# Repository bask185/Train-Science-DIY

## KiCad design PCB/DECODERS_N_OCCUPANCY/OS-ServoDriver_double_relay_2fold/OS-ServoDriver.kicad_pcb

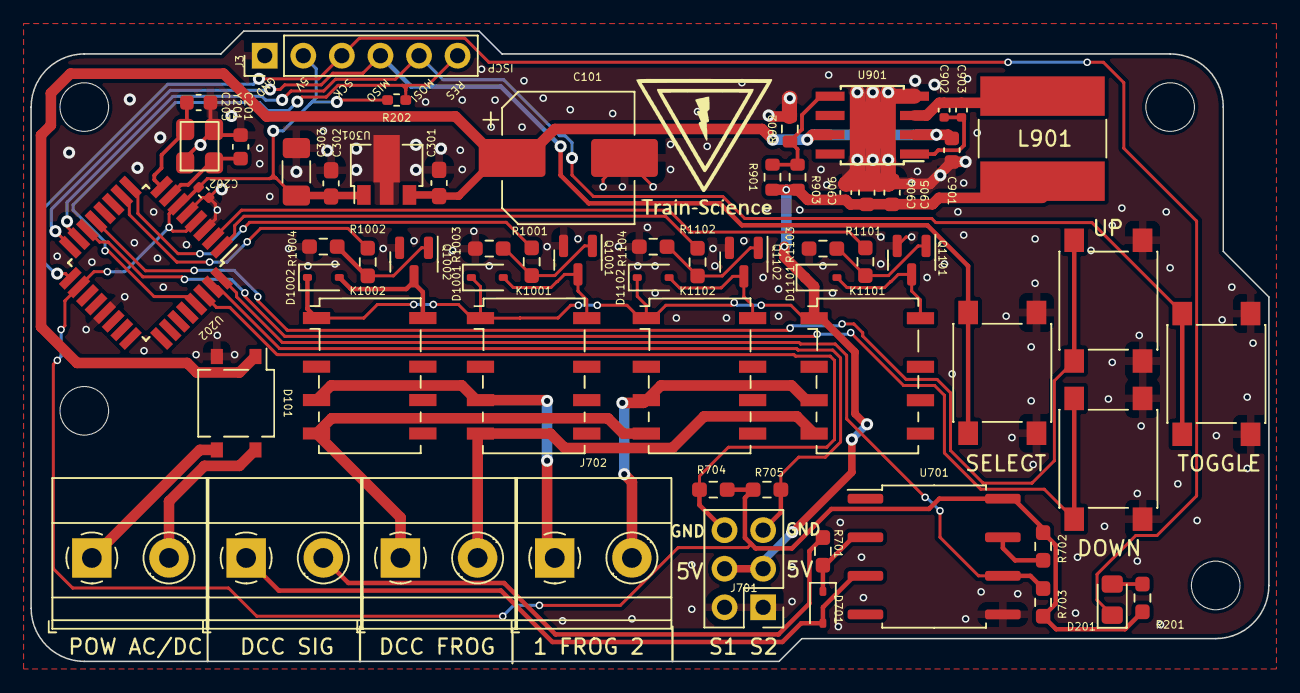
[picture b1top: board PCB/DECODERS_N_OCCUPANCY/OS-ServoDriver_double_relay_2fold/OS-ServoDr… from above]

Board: 2 copper layers, 81.5 x 41.5 mm, 62 parts (0 on the bottom side), 41 nets.

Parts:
C101: 1000uF; CP_Elec_8x10.5
C201, C203: 12pF; C_0603_1608Metric
C202, C902, C906: 100nF; C_0402_1005Metric
C301: 330nF; C_0603_1608Metric_Pad1.08x0.95mm_HandSolder
C302: 100nF; C_0603_1608Metric_Pad1.08x0.95mm_HandSolder
C303: 100uF; C_1206_3216Metric_Pad1.33x1.80mm_HandSolder
C901, C904, C905: 22uF; C_0603_1608Metric
C903: 22nF; C_0402_1005Metric
D101: MB10S; TO-269AA
D201: LED; LED_0805_2012Metric_Pad1.15x1.40mm_HandSolder
D701, D1001, D1002, D1101, D1102: 1N4148WS; D_SOD-323
J3: ICSP; PinHeader_1x06_P2.54mm_Vertical
J101: POWER; TerminalBlock_Phoenix_MKDS-1,5-2-5.08_1x02_P5.08mm_Horizont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
J102: DCC_FROG; TerminalBlock_Phoenix_MKDS-1,5-2-5.08_1x02_P5.08mm_Horizont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
J103: DCC_SIGNAL; TerminalBlock_Phoenix_MKDS-1,5-2-5.08_1x02_P5.08mm_Horizont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
J701: Servo; PinHeader_2x03_P2.54mm_Vertical
J702: Frogs; TerminalBlock_Phoenix_MKDS-1,5-2-5.08_1x02_P5.08mm_Horizont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
K1001, K1002, K1101, K1102: G6K-2F-Y-TR DC5; Relay_DPDT_Omron_G6K-2F-Y
L901: L; L_Bourns-SRN8040_8x8.15mm
Q1001, Q1002, Q1101, Q1102: AO3400A; SOT-23
R201: 6k2; R_0603_1608Metric_Pad0.98x0.95mm_HandSolder
R202: 10k; R_0402_1005Metric_Pad0.72x0.64mm_HandSolder
R701: 1k5; R_0603_smalltext
R702, R703, R704, R705, R1003, R1004, R1103, R1104: 10k; R_0603_smalltext
R901: 220k; R_0603_1608Metric
R902: 20k; R_0603_1608Metric
R903: 150k; R_0603_1608Metric
R1001, R1002, R1101, R1102: 22R; R_0603_smalltext
SW101, SW102, SW103, SW104: SW_Push; tactile_SMD_6mm
U202: ATmega328-A; TQFP-32_7x7mm_P0.8mm
U301: L78L05_SOT89; SOT-89-3
U701: 6N137; SOP-8_6.62x9.15mm_P2.54mm
U901: MT2499A; TI_SO-PowerPAD-8
Y201: Crystal_GND2; crystal_arduino

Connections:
+5V: C202.1, C302.1, C303.1, J3.2, R201.1, R202.2, R702.1, R703.1, R704.1, R705.1, U202.4 (VCC), U202.6 (VCC), U202.18 (AVCC), U301.1 (OUT), U701.8 (VCC)
+5VA: C904.1, C905.1, C906.1, D1001.1 (K), D1002.1 (K), D1101.1 (K), D1102.1 (K), J701.3, J701.4, K1001.1, K1002.1, K1101.1, K1102.1, L901.2, R901.1, R903.2
/DCC/DCC_TTL: R703.2, U202.32 (PD2), U701.6 (VO)
/DCC_FROG_A: J102.2, K1001.4, K1101.4
/DCC_FROG_B: J102.1, K1002.4, K1102.4
/DCC_SIG_A: J103.2, R701.1
/DCC_SIG_B: D701.2 (A), J103.1, U701.3 (C)
/Servo3-4/Frog1: J702.2, K1101.3, K1102.3
/Servo3-4/Frog2: J702.1, K1001.3, K1002.3
/Servo3-4/Relay1: R1101.1, U202.2 (PD4)
/Servo3-4/Relay2: R1102.1, U202.1 (PD3)
/Servo3-4/Relay3: R1001.1, U202.9 (PD5)
/Servo3-4/Relay4: R1002.1, U202.10 (PD6)
/Servo3-4/Servo1: J701.6, R704.2, U202.30 (PD0)
/Servo3-4/Servo2: J701.5, R705.2, U202.31 (PD1)
/atmega/LED: D201.1 (K), J3.3, U202.17 (PB5)
/atmega/X1: C201.2, U202.7 (XTAL1/PB6), Y201.1
/atmega/X2: C203.2, U202.8 (XTAL2/PB7), Y201.3
/atmega/reset: J3.6, R202.1, U202.29 (~RESET/PC6)
/down: SW103.2, U202.14 (PB2)
/select: J3.4, SW101.2, U202.16 (PB4)
/toggle: J3.5, SW102.2, U202.15 (PB3)
/up: SW104.2, U202.13 (PB1)
GND: C101.2, C201.1, C202.2, C203.1, C301.2, C302.2, C303.2, C901.2, C904.2, C905.2, C906.2, D101.2 (-), J3.1, J701.1, J701.2, Q1001.2 (S), Q1002.2 (S), Q1101.2 (S), Q1102.2 (S), R902.2, R1003.1, R1004.1, R1103.1, R1104.1, SW101.1, SW102.1, SW103.1, SW104.1, U202.3 (GND), U202.5 (GND), U202.21 (GND), U301.2 (GND), U701.5 (GND), U901.4 (GND), U901.9 (GND), Y201.2 (GND), Y201.4 (GND)
unnamed: D201.2 (A), R201.2
unnamed: D701.1 (K), R701.2, U701.2 (A)
unnamed: D1001.2 (A), K1001.8, Q1001.3 (D)
unnamed: D1002.2 (A), K1002.8, Q1002.3 (D)
unnamed: D1101.2 (A), K1101.8, Q1101.3 (D)
unnamed: D1102.2 (A), K1102.8, Q1102.3 (D)
unnamed: D101.3, J101.1
unnamed: D101.4, J101.2
unnamed: Q1001.1 (G), R1001.2, R1003.2
unnamed: Q1002.1 (G), R1002.2, R1004.2
unnamed: Q1101.1 (G), R1101.2, R1103.2
unnamed: Q1102.1 (G), R1102.2, R1104.2
unnamed: R702.2, U701.7 (EN)
unnamed: C902.1, C903.1, U901.1 (BS)
unnamed: R901.2, R902.1, R903.1, U901.5 (FB)
unnamed: C902.2, C903.2, L901.1, U901.3 (SW)
VCC: C101.1, C301.1, C901.1, D101.1 (+), U301.3 (IN), U901.2 (Vin), U901.7 (EN)

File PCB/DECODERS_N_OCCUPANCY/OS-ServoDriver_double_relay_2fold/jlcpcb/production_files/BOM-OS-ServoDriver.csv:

Comment,Designator,Footprint,LCSC
6N137,U701,SOP-8_6.62x9.15mm_P2.54mm,C110020
Crystal_GND2,Y201,crystal_arduino,C13738
100nF,C302,C_0603_1608Metric_Pad1.08x0.95mm_HandSolder,C14663
ATmega328-A,U202,TQFP-32_7x7mm_P0.8mm,C14877
100uF,C303,C_1206_3216Metric_Pad1.33x1.80mm_HandSolder,C15008
22nF,C903,C_0402_1005Metric,C1532
330nF,C301,C_0603_1608Metric_Pad1.08x0.95mm_HandSolder,C1615
AO3400A,"Q1001,Q1002,Q1101,Q1102",SOT-23,C20917
1N4148WS,"D1001,D1002,D1101,D1102,D701",D_SOD-323,C2128
150k,R903,R_0603_1608Metric,C22807
1k5,R701,R_0603_smalltext,C22843
220k,R901,R_0603_1608Metric,C22961
22R,"R1001,R1002,R1101,R1102",R_0603_smalltext,C23345
MB10S,D101,TO-269AA,C2488
10k,R202,R_0402_1005Metric_Pad0.72x0.64mm_HandSolder,C25744
10k,"R1003,R1004,R1103,R1104,R702,R703,R704,R705",R_0603_smalltext,C25804
L,L901,L_Bourns-SRN8040_8x8.15mm,C2929438
SW_Push,"SW101,SW102,SW103,SW104",tactile_SMD_6mm,C294567
MT2499A,U901,TI_SO-PowerPAD-8,C3007555
100nF,"C202,C902,C906",C_0402_1005Metric,C307331
12pF,"C201,C203",C_0603_1608Metric,C38523
6k2,R201,R_0603_1608Metric_Pad0.98x0.95mm_HandSolder,C4260
20k,R902,R_0603_1608Metric,C4328
22uF,"C901,C904,C905",C_0603_1608Metric,C45783
G6K-2F-Y-TR DC5,"K1001,K1002,K1101,K1102",Relay_DPDT_Omron_G6K-2F-Y,C47190
1000uF,C101,CP_Elec_8x10.5,C5162347
Servo,J701,PinHeader_2x03_P2.54mm_Vertical,C65114
L78L05_SOT89,U301,SOT-89-3,C71136
LED,D201,LED_0805_2012Metric_Pad1.15x1.40mm_HandSolder,C84256
POWER,"J101,J102,J103,J702","TerminalBlock_Phoenix_MKDS-1,5-2-5.08_1x02_P5.08mm_Horizontal",C8465

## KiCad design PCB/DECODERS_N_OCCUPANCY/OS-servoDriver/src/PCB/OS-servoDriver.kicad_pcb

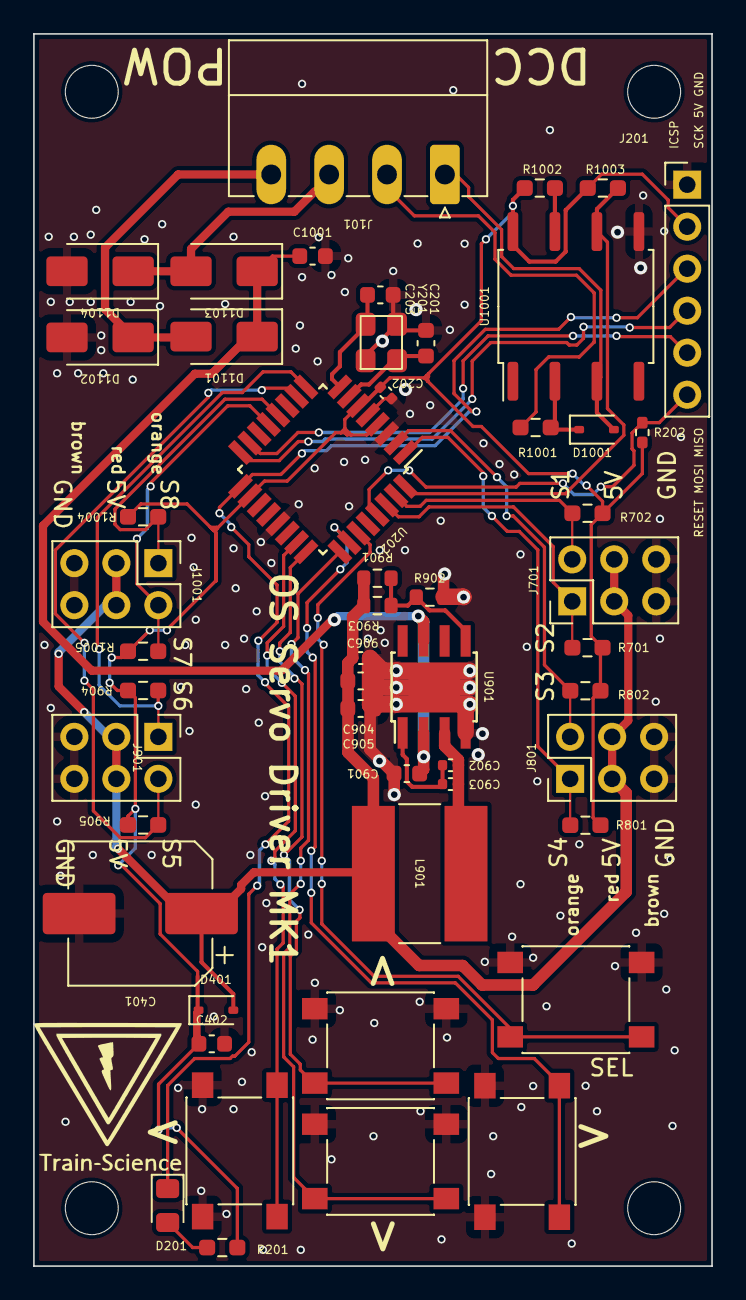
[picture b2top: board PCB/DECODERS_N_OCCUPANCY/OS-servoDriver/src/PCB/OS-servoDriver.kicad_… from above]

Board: 2 copper layers, 41.0 x 74.5 mm, 51 parts (0 on the bottom side), 34 nets.

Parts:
C201, C203: 12pF; C_0603_1608Metric
C202, C902, C906: 100nF; C_0402_1005Metric
C401: 1000uF; CP_Elec_8x10.5
C402, C901, C904, C905: 22uF; C_0603_1608Metric
C903: 22nF; C_0402_1005Metric
C1001: 100nF; C_0603_1608Metric
D201: LED; LED_0805_2012Metric_Pad1.15x1.40mm_HandSolder
D401, D1001: 1N4148WS; D_SOD-323
D1101, D1102, D1103, D1104: SS53; D_SMA
J101: Screw_Terminal_01x04; PhoenixContact_MC_1,5_4-G-3.5_1x04_P3.50mm_Horizontal
J201: ICSP; PinHeader_1x06_P2.54mm_Vertical
J701, J801, J901, J1001: Conn_02x03_Odd_Even; PinHeader_2x03_P2.54mm_Vertical
L901: L; L_Bourns-SRN8040_8x8.15mm
R201: 6k2; R_0603_1608Metric_Pad0.98x0.95mm_HandSolder
R202: 10k; R_0402_1005Metric_Pad0.72x0.64mm_HandSolder
R701, R702, R801, R802, R904, R905, R1002, R1003, R1004, R1005: 10k; R_0603_smalltext
R901: 220k; R_0603_1608Metric
R902: 20k; R_0603_1608Metric
R903: 150k; R_0603_1608Metric
R1001: 1k; R_0603_smalltext
SW601, SW602, SW603, SW604, SW605: SW_Push; tactile_SMD_6mm
U202: ATmega328-A; TQFP-32_7x7mm_P0.8mm
U901: MT2499A; TI_SO-PowerPAD-8
U1001: 6N137; SOP-8_6.62x9.15mm_P2.54mm
Y201: Crystal_GND2; crystal_arduino

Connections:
+5V: C202.1, C402.1, D401.1 (K), J201.2, R201.1, R202.2, R701.2, R702.2, R801.2, R802.2, R904.2, R905.2, R1002.1, R1003.1, R1004.2, R1005.2, U202.4 (VCC), U202.6 (VCC), U202.18 (AVCC), U1001.8 (VCC)
+5VA: C401.1, C904.1, C905.1, C906.1, D401.2 (A), J701.3, J701.4, J801.3, J801.4, J901.3, J901.4, J1001.3, J1001.4, L901.2, R901.1, R903.2
/DCC/DCC_A: J101.2, R1001.1
/DCC/DCC_B: D1001.2 (A), J101.1, U1001.3 (C)
/DCC/DCC_TTL: R1003.2, U202.32 (PD2), U1001.6 (VO)
/D_bridge/AC_1: D1101.2 (A), D1102.1 (K), J101.4
/D_bridge/AC_2: D1103.2 (A), D1104.1 (K), J101.3
/atmega/LED: D201.1 (K), J201.3, U202.17 (PB5)
/atmega/MISO: J201.4, U202.16 (PB4)
/atmega/MOSI: J201.5, U202.15 (PB3)
/atmega/X1: C201.2, U202.7 (XTAL1/PB6), Y201.1
/atmega/X2: C203.2, U202.8 (XTAL2/PB7), Y201.3
/atmega/bus1.pin1: J701.1, R701.1, U202.30 (PD0)
/atmega/bus1.pin2: J701.2, R702.1, U202.31 (PD1)
/atmega/bus2.pin1: J801.1, R801.1, U202.1 (PD3)
/atmega/bus2.pin2: J801.2, R802.1, U202.2 (PD4)
/atmega/bus3.pin1: J901.1, R904.1, U202.9 (PD5)
/atmega/bus3.pin2: J901.2, R905.1, U202.10 (PD6)
/atmega/bus4.pin1: J1001.1, R1004.1, U202.12 (PB0)
/atmega/bus4.pin2: J1001.2, R1005.1, U202.13 (PB1)
/atmega/reset: J201.6, R202.1, U202.29 (~RESET/PC6)
/atmega/sw1: SW601.2, U202.23 (PC0)
/atmega/sw2: SW602.2, U202.24 (PC1)
/atmega/sw3: SW603.2, U202.25 (PC2)
/atmega/sw4: SW604.2, U202.26 (PC3)
/atmega/sw5: SW605.2, U202.27 (PC4)
GND: C201.1, C202.2, C203.1, C401.2, C402.2, C901.2, C904.2, C905.2, C906.2, C1001.2, D1102.2 (A), D1104.2 (A), J201.1, J701.5, J701.6, J801.5, J801.6, J901.5, J901.6, J1001.5, J1001.6, R902.2, SW601.1, SW602.1, SW603.1, SW604.1, SW605.1, U202.3 (GND), U202.5 (GND), U202.21 (GND), U901.4 (GND), U901.9 (GND), U1001.5 (GND), Y201.2 (GND), Y201.4 (GND)
unnamed: D201.2 (A), R201.2
unnamed: D1001.1 (K), R1001.2, U1001.2 (A)
unnamed: C902.1, C903.1, U901.1 (BS)
unnamed: R901.2, R902.1, R903.1, U901.5 (FB)
unnamed: C902.2, C903.2, L901.1, U901.3 (SW)
unnamed: R1002.2, U1001.7 (EN)
VCC: C901.1, C1001.1, D1101.1 (K), D1103.1 (K), U901.2 (Vin), U901.7 (EN)

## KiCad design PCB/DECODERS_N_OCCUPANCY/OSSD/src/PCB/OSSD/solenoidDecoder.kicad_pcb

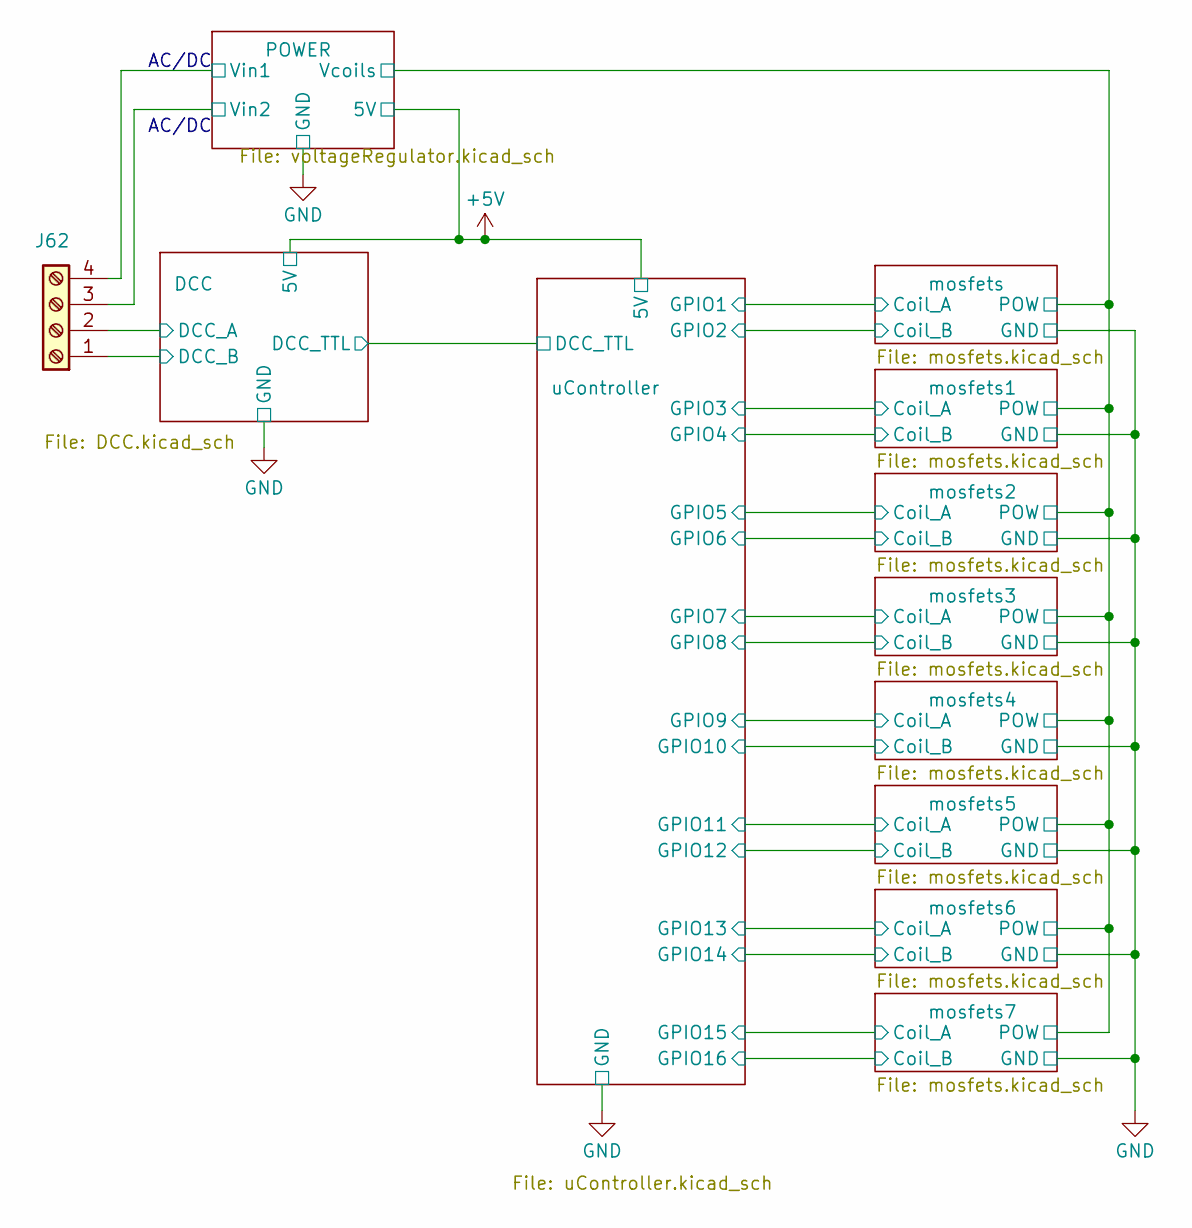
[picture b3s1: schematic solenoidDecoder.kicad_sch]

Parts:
J62: Screw_Terminal_01x04; TerminalBlock_Phoenix_MKDS-1,5-4-5.08_1x04_P5.08mm_Horizont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

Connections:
/DCC/DCC_A: J62.2; also elsewhere on the board
/DCC/DCC_B: J62.1; also elsewhere on the board
/POWER/Vin1: J62.4; also elsewhere on the board
/POWER/Vin2: J62.3; also elsewhere on the board

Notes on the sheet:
AC/DC

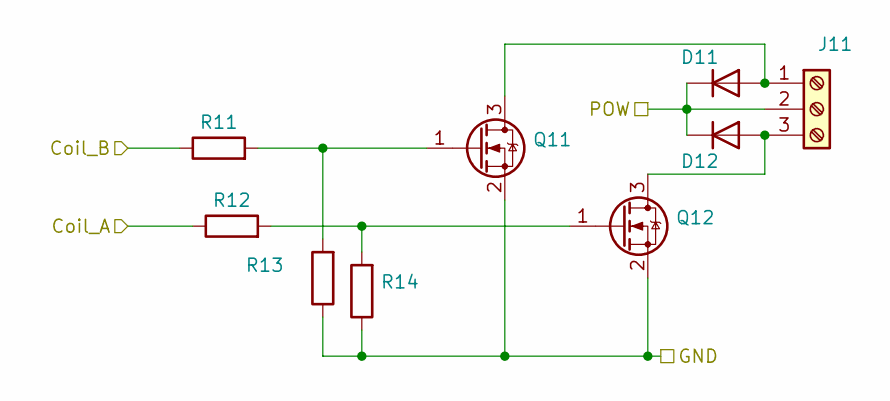
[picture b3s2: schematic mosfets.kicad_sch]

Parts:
D11, D12: D_SMA; JLCPCB Part# C8678
J11: TerminalBlock_Phoenix_MKDS-1,5-3-5.08_1x03_P5.08mm_Horizont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
Q11, Q12: SOT-23; JLCPCB Part# C20917
R11, R12: R_0603_1608Metric_Pad0.98x0.95mm_HandSolder; JLCPCB Part# C23345
R13, R14: R_0603_1608Metric_Pad0.98x0.95mm_HandSolder; JLCPCB Part# C25804

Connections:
/POWER/Vcoils: D11.1 (K), D12.1 (K), J11.2; also elsewhere on the board
/uController/GPIO1: R12.1; also elsewhere on the board
/uController/GPIO2: R11.1; also elsewhere on the board
GND: Q11.2 (S), Q12.2 (S), R13.1, R14.1; also elsewhere on the board
unnamed: D11.2 (A), J11.1, Q11.3 (D)
unnamed: D12.2 (A), J11.3, Q12.3 (D)
unnamed: Q11.1 (G), R11.2, R13.2
unnamed: Q12.1 (G), R12.2, R14.2

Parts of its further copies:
D21, D22, D31, D32, D41, D42, D51, D52, D61, D62, D71, D72, D81, D82: D_SMA; JLCPCB Part# C8678
J21, J31, J41, J51, J61, J71, J81: TerminalBlock_Phoenix_MKDS-1,5-3-5.08_1x03_P5.08mm_Horizont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
Q21, Q22, Q31, Q32, Q41, Q42, Q51, Q52, Q61, Q62, Q71, Q72, Q81, Q82: SOT-23; JLCPCB Part# C20917
R21, R22, R31, R32, R41, R42, R51, R52, R61, R62, R71, R72, R81, R82: R_0603_1608Metric_Pad0.98x0.95mm_HandSolder; JLCPCB Part# C23345
R23, R24, R33, R34, R43, R44, R53, R54, R63, R64, R73, R74, R83, R84: R_0603_1608Metric_Pad0.98x0.95mm_HandSolder; JLCPCB Part# C25804

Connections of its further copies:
/POWER/Vcoils: D21.1 (K), D22.1 (K), D31.1 (K), D32.1 (K), D41.1 (K), D42.1 (K), D51.1 (K), D52.1 (K), D61.1 (K), D62.1 (K), D71.1 (K), D72.1 (K), D81.1 (K), D82.1 (K), J21.2, J31.2, J41.2, J51.2, J61.2, J71.2, J81.2; also elsewhere on the board
/uController/GPIO3: R22.1; also elsewhere on the board
/uController/GPIO4: R21.1; also elsewhere on the board
/uController/GPIO5: R32.1; also elsewhere on the board
/uController/GPIO6: R31.1; also elsewhere on the board
/uController/GPIO7: R42.1; also elsewhere on the board
/uController/GPIO8: R41.1; also elsewhere on the board
/uController/GPIO9: R52.1; also elsewhere on the board
/uController/GPIO10: R51.1; also elsewhere on the board
/uController/GPIO11: R62.1; also elsewhere on the board
/uController/GPIO12: R61.1; also elsewhere on the board
/uController/GPIO13: R72.1; also elsewhere on the board
/uController/GPIO14: R71.1; also elsewhere on the board
/uController/GPIO15: R82.1; also elsewhere on the board
/uController/GPIO16: R81.1; also elsewhere on the board
GND: Q21.2 (S), Q22.2 (S), Q31.2 (S), Q32.2 (S), Q41.2 (S), Q42.2 (S), Q51.2 (S), Q52.2 (S), Q61.2 (S), Q62.2 (S), Q71.2 (S), Q72.2 (S), Q81.2 (S), Q82.2 (S), R23.1, R24.1, R33.1, R34.1, R43.1, R44.1, R53.1, R54.1, R63.1, R64.1, R73.1, R74.1, R83.1, R84.1; also elsewhere on the board
unnamed: D21.2 (A), J21.1, Q21.3 (D)
unnamed: D22.2 (A), J21.3, Q22.3 (D)
unnamed: D31.2 (A), J31.1, Q31.3 (D)
unnamed: D32.2 (A), J31.3, Q32.3 (D)
unnamed: D41.2 (A), J41.1, Q41.3 (D)
unnamed: D42.2 (A), J41.3, Q42.3 (D)
unnamed: D51.2 (A), J51.1, Q51.3 (D)
unnamed: D52.2 (A), J51.3, Q52.3 (D)
unnamed: D61.2 (A), J61.1, Q61.3 (D)
unnamed: D62.2 (A), J61.3, Q62.3 (D)
unnamed: D71.2 (A), J71.1, Q71.3 (D)
unnamed: D72.2 (A), J71.3, Q72.3 (D)
unnamed: D81.2 (A), J81.1, Q81.3 (D)
unnamed: D82.2 (A), J81.3, Q82.3 (D)
unnamed: Q21.1 (G), R21.2, R23.2
unnamed: Q22.1 (G), R22.2, R24.2
unnamed: Q31.1 (G), R31.2, R33.2
unnamed: Q32.1 (G), R32.2, R34.2
unnamed: Q41.1 (G), R41.2, R43.2
unnamed: Q42.1 (G), R42.2, R44.2
unnamed: Q51.1 (G), R51.2, R53.2
unnamed: Q52.1 (G), R52.2, R54.2
unnamed: Q61.1 (G), R61.2, R63.2
unnamed: Q62.1 (G), R62.2, R64.2
unnamed: Q71.1 (G), R71.2, R73.2
unnamed: Q72.1 (G), R72.2, R74.2
unnamed: Q81.1 (G), R81.2, R83.2
unnamed: Q82.1 (G), R82.2, R84.2

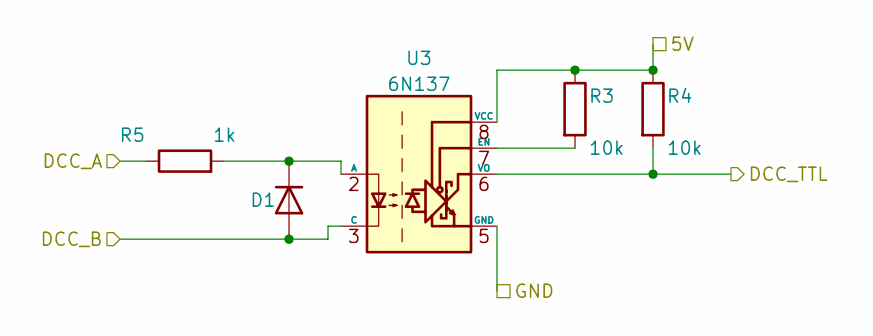
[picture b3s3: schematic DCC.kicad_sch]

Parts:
D1: D; D_SOD-323; JLCPCB Part# C2128
R3, R4: 10k; R_0805_2012Metric_Pad1.20x1.40mm_HandSolder; JLCPCB Part# C17414
R5: 1k; R_0805_2012Metric_Pad1.20x1.40mm_HandSolder; JLCPCB Part# C17513
U3: 6N137; SOP-8_6.62x9.15mm_P2.54mm; JLCPCB Part# C110020

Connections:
+5V: R3.1, R4.1, U3.8 (VCC); also elsewhere on the board
/DCC/DCC_A: R5.1; also elsewhere on the board
/DCC/DCC_B: D1.2 (A), U3.3 (C); also elsewhere on the board
/DCC/DCC_TTL: R4.2, U3.6 (VO); also elsewhere on the board
GND: U3.5 (GND); also elsewhere on the board
unnamed: D1.1 (K), R5.2, U3.2 (A)
unnamed: R3.2, U3.7 (EN)

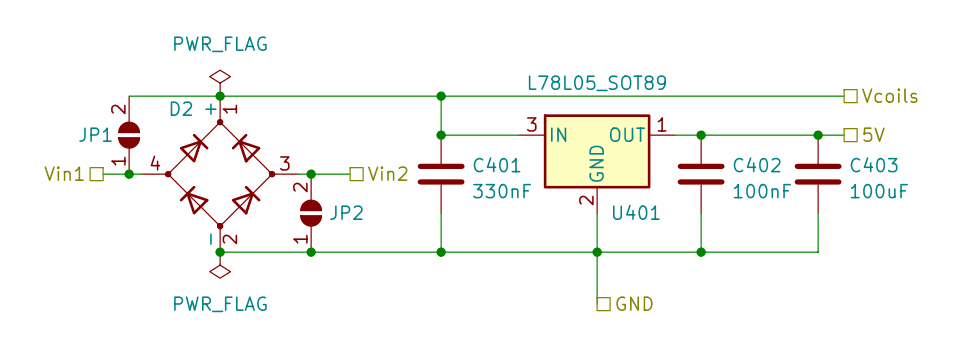
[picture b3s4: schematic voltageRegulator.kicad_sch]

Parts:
C401: 330nF; C_0603_1608Metric_Pad1.08x0.95mm_HandSolder; JLCPCB Part# C1615
C402: 100nF; C_0603_1608Metric_Pad1.08x0.95mm_HandSolder; JLCPCB Part# C14663
C403: 100uF; C_1206_3216Metric_Pad1.33x1.80mm_HandSolder; JLCPCB Part# C15008
D2: 4A rectifier; JLCPCB Part# C169511
JP1, JP2: SolderJumper_2_Open; SolderJumper-2_P1.3mm_Open_RoundedPad1.0x1.5mm
U401: L78L05_SOT89; SOT-89-3; JLCPCB Part# C71136

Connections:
+5V: C402.1, C403.1, U401.1 (OUT); also elsewhere on the board
/POWER/Vcoils: C401.1, D2.1 (+), JP1.2 (B), U401.3 (IN); also elsewhere on the board
/POWER/Vin1: D2.4, JP1.1 (A); also elsewhere on the board
/POWER/Vin2: D2.3, JP2.2 (B); also elsewhere on the board
GND: C401.2, C402.2, C403.2, D2.2 (-), JP2.1 (A), U401.2 (GND); also elsewhere on the board

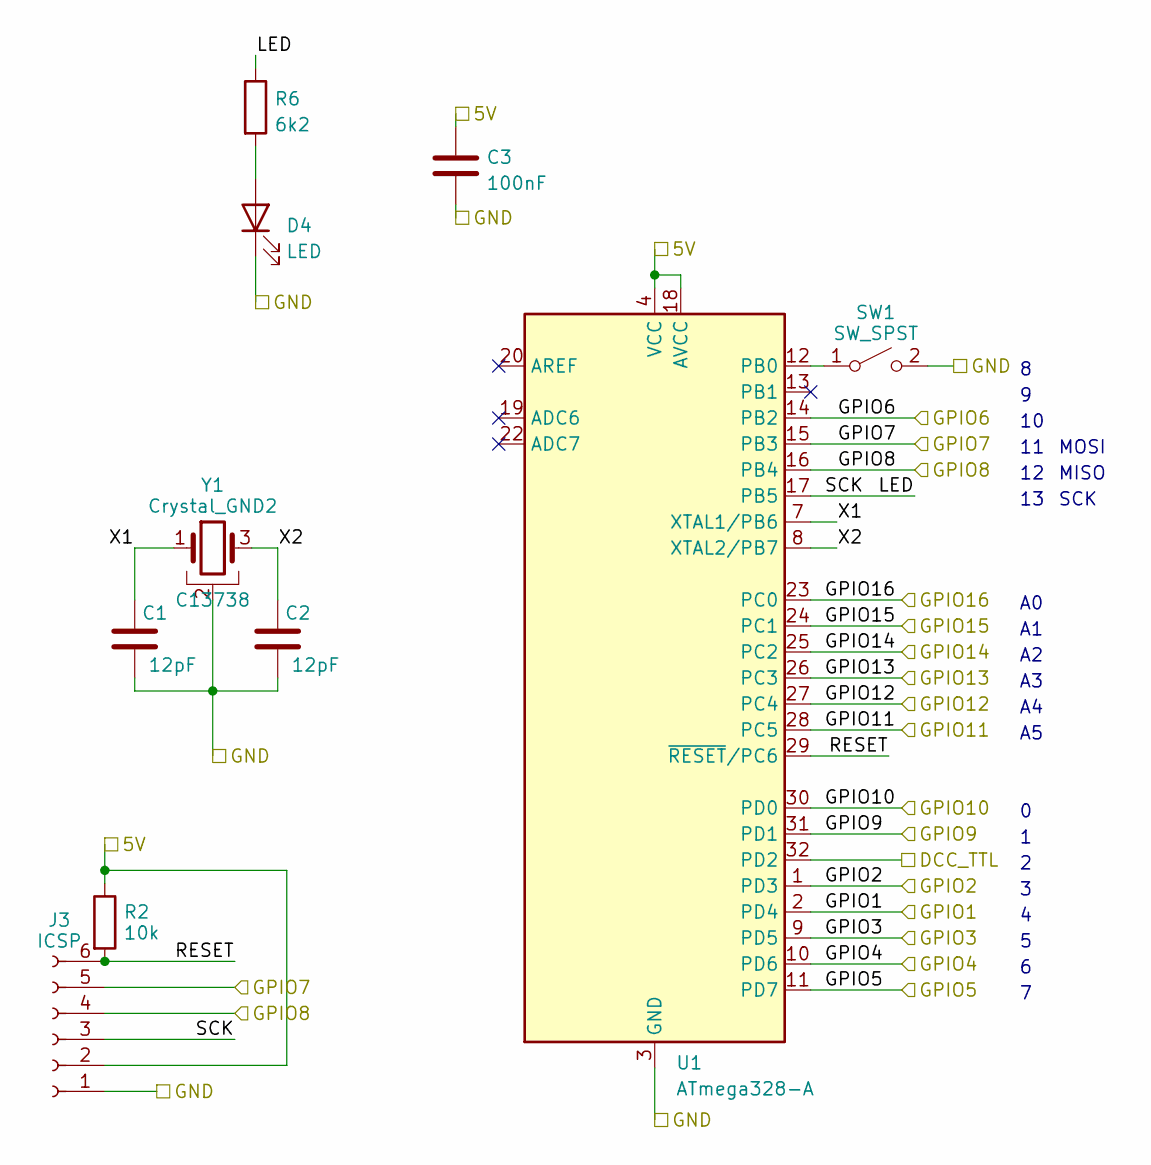
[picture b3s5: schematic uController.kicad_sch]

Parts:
C1, C2: 12pF; C_0402_1005Metric_Pad0.74x0.62mm_HandSolder; JLCPCB Part# C1547
C3: 100nF; C_0603_1608Metric_Pad1.08x0.95mm_HandSolder; JLCPCB Part# C14663
D4: LED; LED_0805_2012Metric_Pad1.15x1.40mm_HandSolder; JLCPCB Part# C84256
J3: ICSP; PinHeader_1x06_P2.54mm_Vertical
R2: 10k; R_0402_1005Metric_Pad0.72x0.64mm_HandSolder; JLCPCB Part# C25744
R6: 6k2; R_0603_1608Metric_Pad0.98x0.95mm_HandSolder; JLCPCB Part# C4260
SW1: SW_SPST; SW_SPST_SKQG_WithStem; JLCPCB Part# C318884
U1: ATmega328-A; TQFP-32_7x7mm_P0.8mm; JLCPCB Part# C14877
Y1: Crystal_GND2; crystal_arduino; JLCPCB Part# C13738

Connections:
+5V: C3.2, J3.2, R2.1, U1.4 (VCC), U1.6 (VCC), U1.18 (AVCC); also elsewhere on the board
/DCC/DCC_TTL: U1.32 (PD2); also elsewhere on the board
/uController/GPIO1: U1.2 (PD4); also elsewhere on the board
/uController/GPIO2: U1.1 (PD3); also elsewhere on the board
/uController/GPIO3: U1.9 (PD5); also elsewhere on the board
/uController/GPIO4: U1.10 (PD6); also elsewhere on the board
/uController/GPIO5: U1.11 (PD7); also elsewhere on the board
/uController/GPIO6: U1.14 (PB2); also elsewhere on the board
/uController/GPIO7: J3.5, U1.15 (PB3); also elsewhere on the board
/uController/GPIO8: J3.4, U1.16 (PB4); also elsewhere on the board
/uController/GPIO9: U1.31 (PD1); also elsewhere on the board
/uController/GPIO10: U1.30 (PD0); also elsewhere on the board
/uController/GPIO11: U1.28 (PC5); also elsewhere on the board
/uController/GPIO12: U1.27 (PC4); also elsewhere on the board
/uController/GPIO13: U1.26 (PC3); also elsewhere on the board
/uController/GPIO14: U1.25 (PC2); also elsewhere on the board
/uController/GPIO15: U1.24 (PC1); also elsewhere on the board
/uController/GPIO16: U1.23 (PC0); also elsewhere on the board
/uController/LED: J3.3, R6.1, U1.17 (PB5)
/uController/RESET: J3.6, R2.2, U1.29 (~RESET/PC6)
/uController/X1: C1.2, U1.7 (XTAL1/PB6), Y1.1
/uController/X2: C2.2, U1.8 (XTAL2/PB7), Y1.3
GND: C1.1, C2.1, C3.1, D4.1 (K), J3.1, SW1.2 (B), U1.3 (GND), U1.5 (GND), U1.21 (GND), Y1.2 (GND), Y1.4 (GND); also elsewhere on the board
unnamed: D4.2 (A), R6.2
unnamed: SW1.1 (A), U1.12 (PB0)

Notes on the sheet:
MOSI
SCK
MISO

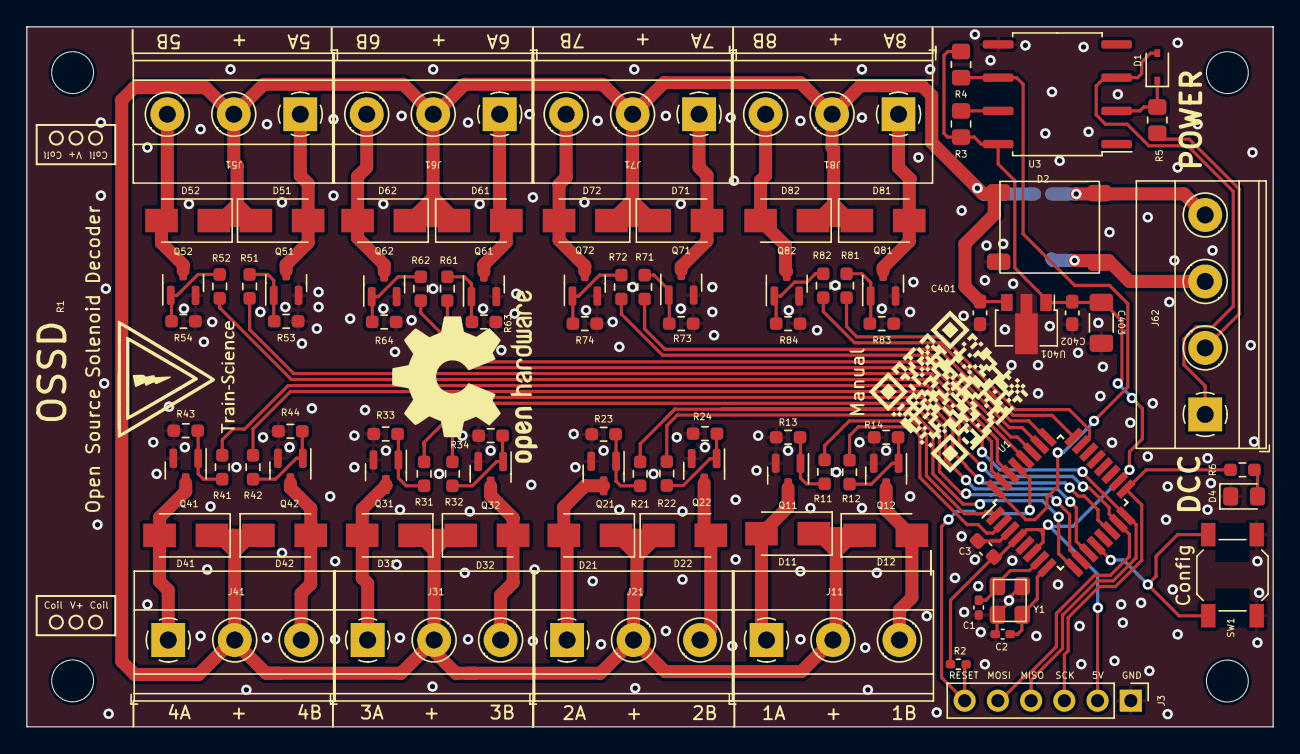
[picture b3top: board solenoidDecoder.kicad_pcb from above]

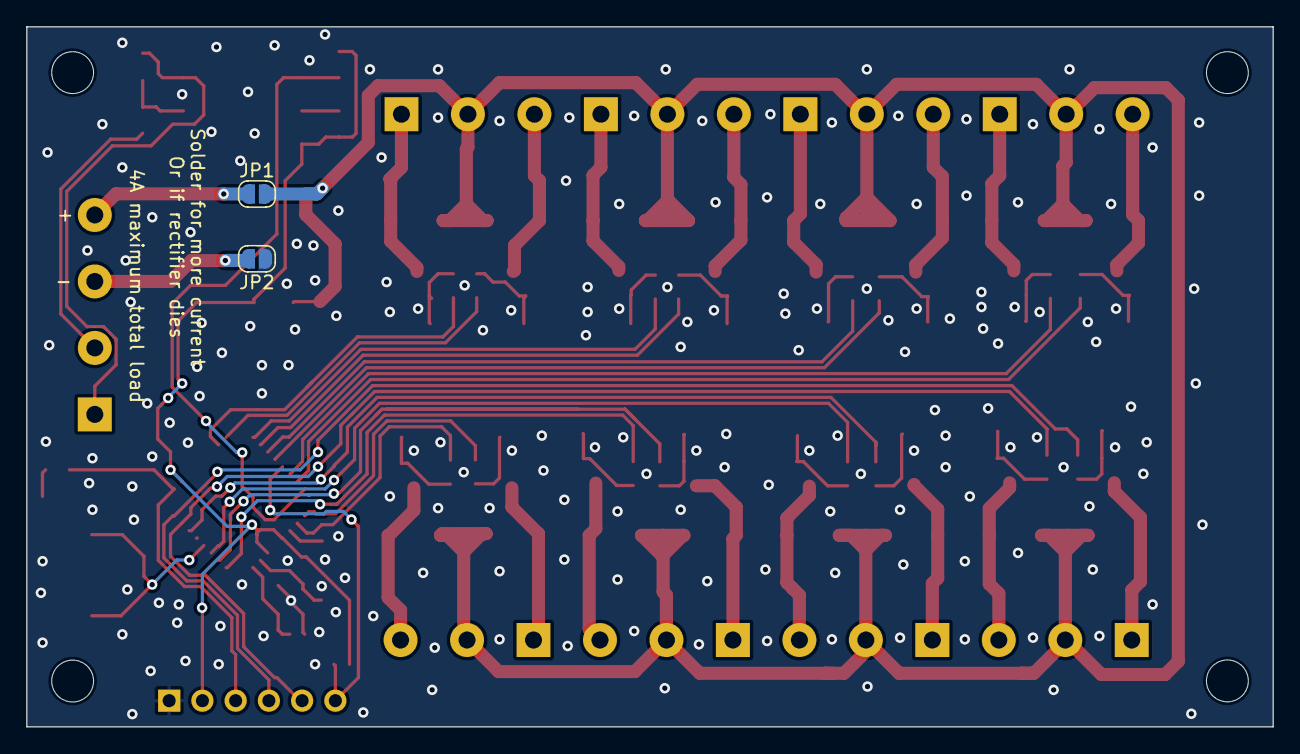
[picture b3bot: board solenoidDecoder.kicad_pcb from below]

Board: 2 copper layers, 95.3 x 53.5 mm, 95 parts (2 on the bottom side), 64 nets.

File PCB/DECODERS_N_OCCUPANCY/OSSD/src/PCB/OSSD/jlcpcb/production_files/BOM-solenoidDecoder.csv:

Comment,Designator,Footprint,LCSC
6N137,U3,SOP-8_6.62x9.15mm_P2.54mm,C110020
Crystal_GND2,Y1,crystal_arduino,C13738
100nF,"C3,C402",C_0603_1608Metric_Pad1.08x0.95mm_HandSolder,C14663
ATmega328-A,U1,TQFP-32_7x7mm_P0.8mm,C14877
100uF,C403,C_1206_3216Metric_Pad1.33x1.80mm_HandSolder,C15008
12pF,"C1,C2",C_0402_1005Metric_Pad0.74x0.62mm_HandSolder,C1547
330nF,C401,C_0603_1608Metric_Pad1.08x0.95mm_HandSolder,C1615
~,D2,4A rectifier,C169511
10k,"R3,R4",R_0805_2012Metric_Pad1.20x1.40mm_HandSolder,C17414
1k,R5,R_0805_2012Metric_Pad1.20x1.40mm_HandSolder,C17513
~,"Q11,Q12,Q21,Q22,Q31,Q32,Q41,Q42,Q51,Q52,Q61,Q62,Q71,Q72,Q81,Q82",SOT-23,C20917
D,D1,D_SOD-323,C2128
~,"R11,R12,R21,R22,R31,R32,R41,R42,R51,R52,R61,R62,R71,R72,R81,R82",R_0603_1608Metric_Pad0.98x0.95mm_HandSolder,C23345
10k,R2,R_0402_1005Metric_Pad0.72x0.64mm_HandSolder,C25744
~,"R13,R14,R23,R24,R33,R34,R43,R44,R53,R54,R63,R64,R73,R74,R83,R84",R_0603_1608Metric_Pad0.98x0.95mm_HandSolder,C25804
SW_SPST,SW1,SW_SPST_SKQG_WithStem,C318884
6k2,R6,R_0603_1608Metric_Pad0.98x0.95mm_HandSolder,C4260
L78L05_SOT89,U401,SOT-89-3,C71136
LED,D4,LED_0805_2012Metric_Pad1.15x1.40mm_HandSolder,C84256
~,"D11,D12,D21,D22,D31,D32,D41,D42,D51,D52,D61,D62,D71,D72,D81,D82",D_SMA,C8678
SolderJumper_2_Open,JP2,SolderJumper-2_P1.3mm_Open_RoundedPad1.0x1.5mm,
SolderJumper_2_Open,JP1,SolderJumper-2_P1.3mm_Open_RoundedPad1.0x1.5mm,
Screw_Terminal_01x04,J62,"TerminalBlock_Phoenix_MKDS-1,5-4-5.08_1x04_P5.08mm_Horizontal",
~,J41,"TerminalBlock_Phoenix_MKDS-1,5-3-5.08_1x03_P5.08mm_Horizontal",
ICSP,J3,PinHeader_1x06_P2.54mm_Vertical,
~,J81,"TerminalBlock_Phoenix_MKDS-1,5-3-5.08_1x03_P5.08mm_Horizontal",
~,J61,"TerminalBlock_Phoenix_MKDS-1,5-3-5.08_1x03_P5.08mm_Horizontal",
~,J51,"TerminalBlock_Phoenix_MKDS-1,5-3-5.08_1x03_P5.08mm_Horizontal",
~,J31,"TerminalBlock_Phoenix_MKDS-1,5-3-5.08_1x03_P5.08mm_Horizontal",
~,J21,"TerminalBlock_Phoenix_MKDS-1,5-3-5.08_1x03_P5.08mm_Horizontal",
~,J71,"TerminalBlock_Phoenix_MKDS-1,5-3-5.08_1x03_P5.08mm_Horizontal",
~,J11,"TerminalBlock_Phoenix_MKDS-1,5-3-5.08_1x03_P5.08mm_Horizontal",

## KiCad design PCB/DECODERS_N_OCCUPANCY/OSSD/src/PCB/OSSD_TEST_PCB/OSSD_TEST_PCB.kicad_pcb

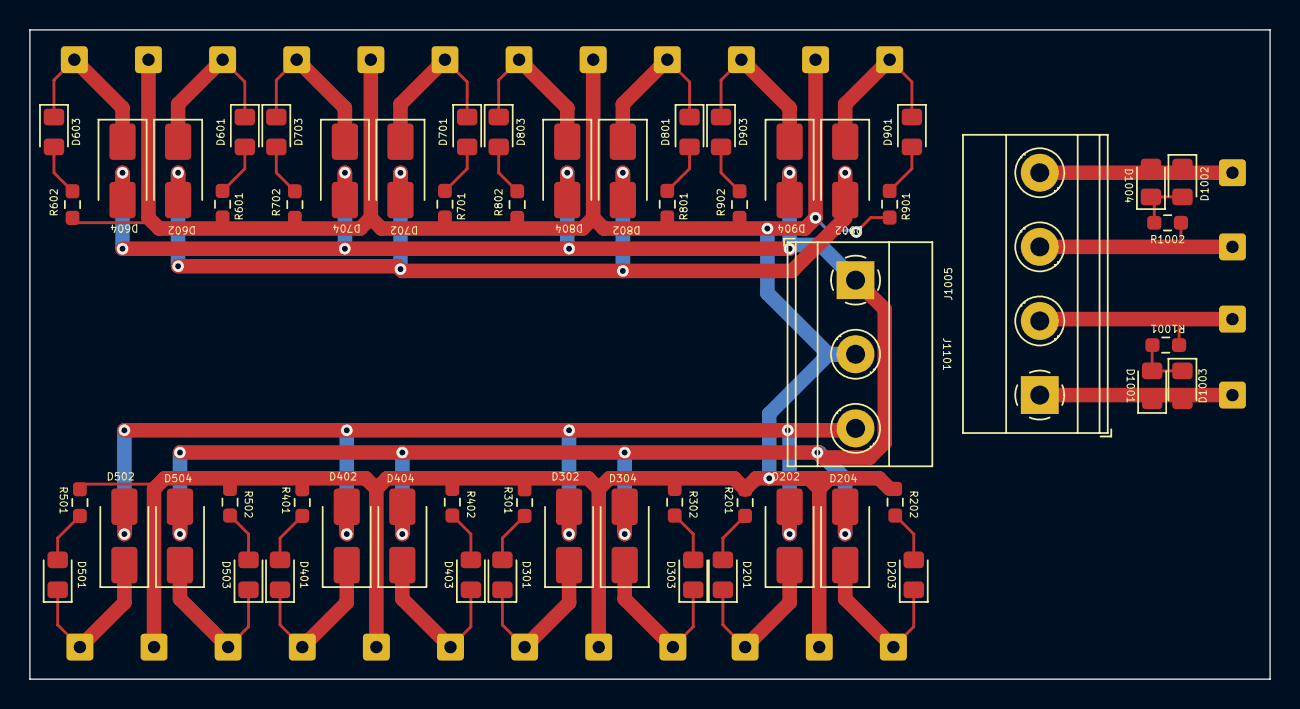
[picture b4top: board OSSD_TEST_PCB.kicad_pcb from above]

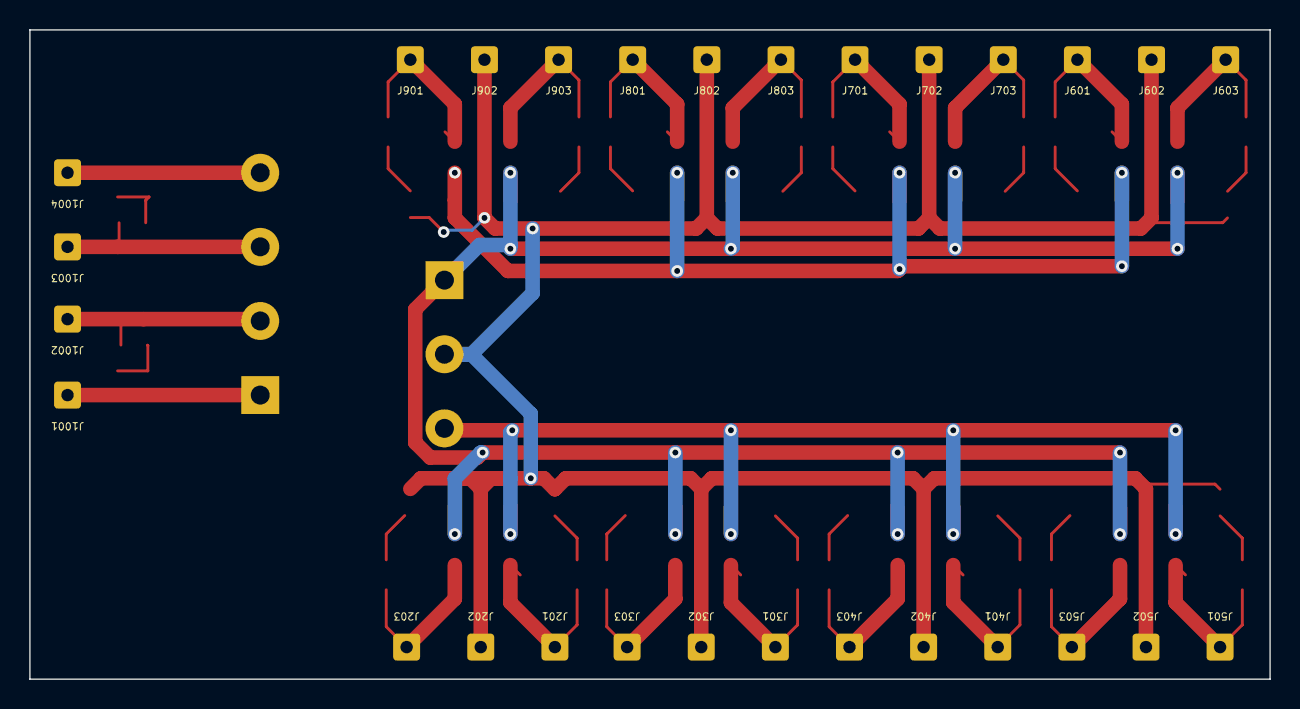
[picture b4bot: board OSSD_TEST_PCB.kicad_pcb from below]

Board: 2 copper layers, 85.0 x 44.5 mm, 84 parts (28 on the bottom side), 41 nets.

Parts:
D201, D203, D301, D303, D401, D403, D501, D503, D601, D603, D701, D703, D801, D803, D901, D903, D1001, D1002, D1003, D1004: LED; LED_0805_2012Metric_Pad1.15x1.40mm_HandSolder
D202, D204, D302, D304, D402, D404, D502, D504, D602, D604, D702, D704, D802, D804, D902, D904: SS53; D_SMA
J201, J202, J203, J301, J302, J303, J401, J402, J403, J501, J502, J503, J601, J602, J603, J701, J702, J703, J801, J802, J803, J901, J902, J903: pogo; pogopin
J1001, J1002, J1003, J1004: POGO; pogopin
J1005: Screw_Terminal_01x04; TerminalBlock_Phoenix_MKDS-1,5-4-5.08_1x04_P5.08mm_Horizont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
J1101: COIL; TerminalBlock_Phoenix_MKDS-1,5-3-5.08_1x03_P5.08mm_Horizont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
R201, R202, R301, R302, R401, R402, R501, R502, R601, R602, R701, R702, R801, R802, R901, R902, R1001, R1002: 10k; R_0603_smalltext

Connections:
A: D202.2 (A), D302.2 (A), D402.2 (A), D502.2 (A), D602.2 (A), D702.2 (A), D802.2 (A), D902.2 (A), J1101.3
B: D204.2 (A), D304.2 (A), D404.2 (A), D504.2 (A), D604.2 (A), D704.2 (A), D804.2 (A), D904.2 (A), J1101.1
unnamed: D201.2 (A), R201.1
unnamed: D201.1 (K), D202.1 (K), J201.1
unnamed: D203.2 (A), R202.1
unnamed: D203.1 (K), D204.1 (K), J203.1
unnamed: D301.2 (A), R301.1
unnamed: D301.1 (K), D302.1 (K), J301.1
unnamed: D303.2 (A), R302.1
unnamed: D303.1 (K), D304.1 (K), J303.1
unnamed: D401.2 (A), R401.1
unnamed: D401.1 (K), D402.1 (K), J401.1
unnamed: D403.2 (A), R402.1
unnamed: D403.1 (K), D404.1 (K), J403.1
unnamed: D501.2 (A), R501.1
unnamed: D501.1 (K), D502.1 (K), J501.1
unnamed: D503.2 (A), R502.1
unnamed: D503.1 (K), D504.1 (K), J503.1
unnamed: D601.2 (A), R601.1
unnamed: D601.1 (K), D602.1 (K), J601.1
unnamed: D603.2 (A), R602.1
unnamed: D603.1 (K), D604.1 (K), J603.1
unnamed: D701.2 (A), R701.1
unnamed: D701.1 (K), D702.1 (K), J701.1
unnamed: D703.2 (A), R702.1
unnamed: D703.1 (K), D704.1 (K), J703.1
unnamed: D801.2 (A), R801.1
unnamed: D801.1 (K), D802.1 (K), J801.1
unnamed: D803.2 (A), R802.1
unnamed: D803.1 (K), D804.1 (K), J803.1
unnamed: D901.2 (A), R901.1
unnamed: D901.1 (K), D902.1 (K), J901.1
unnamed: D903.2 (A), R902.1
unnamed: D903.1 (K), D904.1 (K), J903.1
unnamed: D1001.2 (A), D1003.1 (K), R1001.1
unnamed: D1001.1 (K), D1003.2 (A), J1001.1, J1005.1
unnamed: D1002.2 (A), D1004.1 (K), R1002.1
unnamed: D1002.1 (K), D1004.2 (A), J1004.1, J1005.4
unnamed: J1002.1, J1005.2, R1001.2
unnamed: J1003.1, J1005.3, R1002.2
VCC: J202.1, J302.1, J402.1, J502.1, J602.1, J702.1, J802.1, J902.1, J1101.2, R201.2, R202.2, R301.2, R302.2, R401.2, R402.2, R501.2, R502.2, R601.2, R602.2, R701.2, R702.2, R801.2, R802.2, R901.2, R902.2
